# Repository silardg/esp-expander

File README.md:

# esp-expander

## Main Components
- ESP32-WROOM-32D
- LAN8720
- MCP23017

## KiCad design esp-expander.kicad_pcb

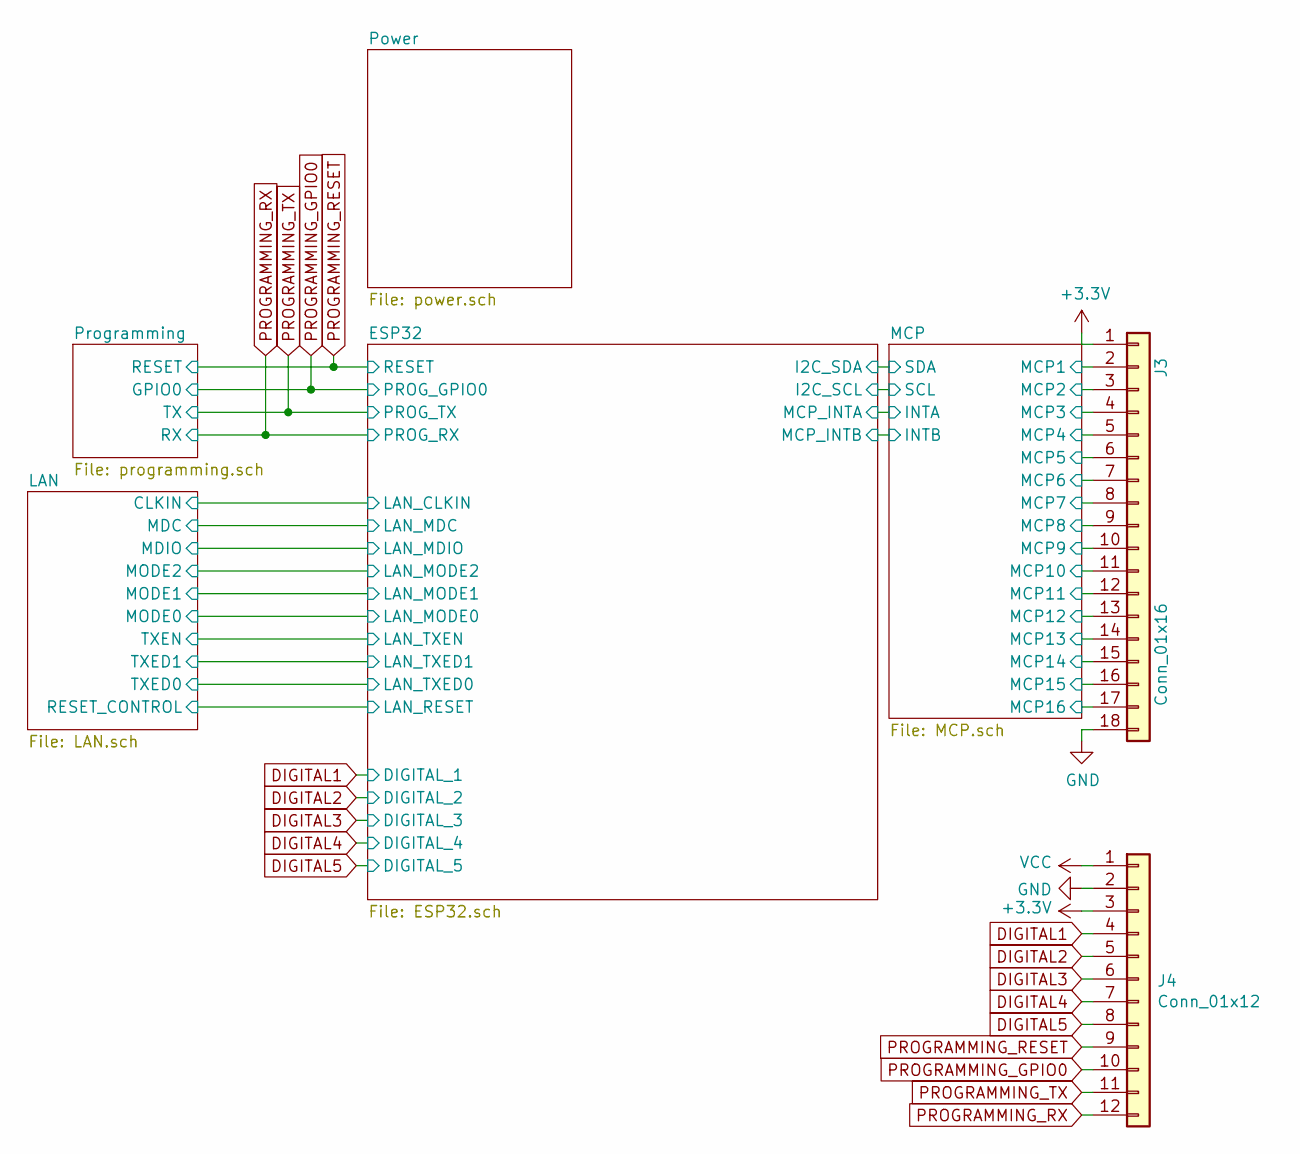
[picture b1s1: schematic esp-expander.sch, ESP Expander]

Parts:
J3: Conn_01x16; PinHeader_1x18_P2.54mm_Vertical; LCSC C725948
J4: Conn_01x12; PinHeader_1x12_P2.54mm_Vertical; LCSC C225487

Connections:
+3V3: J3.1, J4.3; also elsewhere on the board
/MCP/MCP1: J3.2; also elsewhere on the board
/MCP/MCP2: J3.3; also elsewhere on the board
/MCP/MCP3: J3.4; also elsewhere on the board
/MCP/MCP4: J3.5; also elsewhere on the board
/MCP/MCP5: J3.6; also elsewhere on the board
/MCP/MCP6: J3.7; also elsewhere on the board
/MCP/MCP7: J3.8; also elsewhere on the board
/MCP/MCP8: J3.9; also elsewhere on the board
/MCP/MCP9: J3.10; also elsewhere on the board
/MCP/MCP10: J3.11; also elsewhere on the board
/MCP/MCP11: J3.12; also elsewhere on the board
/MCP/MCP12: J3.13; also elsewhere on the board
/MCP/MCP13: J3.14; also elsewhere on the board
/MCP/MCP14: J3.15; also elsewhere on the board
/MCP/MCP15: J3.16; also elsewhere on the board
/MCP/MCP16: J3.17; also elsewhere on the board
DIGITAL1: J4.4; also elsewhere on the board
DIGITAL2: J4.5; also elsewhere on the board
DIGITAL3: J4.6; also elsewhere on the board
DIGITAL4: J4.7; also elsewhere on the board
DIGITAL5: J4.8; also elsewhere on the board
GND: J3.18, J4.2; also elsewhere on the board
PROGRAMMING_GPIO0: J4.10; also elsewhere on the board
PROGRAMMING_RESET: J4.9; also elsewhere on the board
PROGRAMMING_RX: J4.12; also elsewhere on the board
PROGRAMMING_TX: J4.11; also elsewhere on the board
VCC: J4.1; also elsewhere on the board

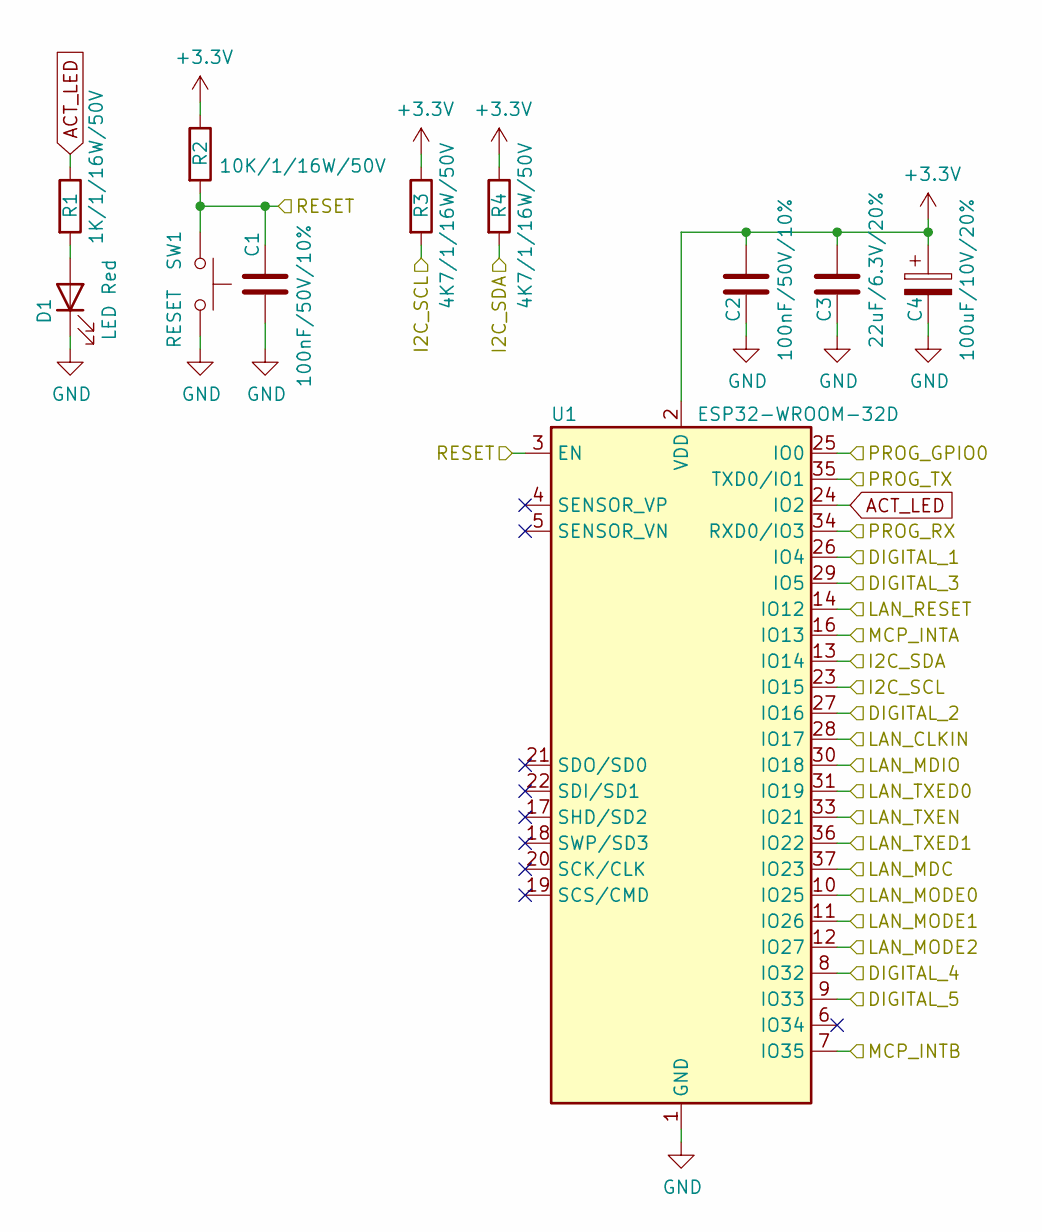
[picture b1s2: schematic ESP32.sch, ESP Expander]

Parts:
C1, C2: 100nF/50V/10%; C_0402_1005Metric; LCSC C307331
C3: 22uF/6.3V/20%; C_0402_1005Metric; LCSC C415703
C4: 100uF/10V/20%; CP_Elec_5x5.4; LCSC C96182
D1: LED Red; LED_0603_1608Metric; LCSC C2286
R1: 1K/1/16W/50V; R_0402_1005Metric; LCSC C11702
R2: 10K/1/16W/50V; R_0402_1005Metric; LCSC C25744
R3, R4: 4K7/1/16W/50V; R_0402_1005Metric; LCSC C25900
SW1: RESET; SW_SPST_EVPBF; LCSC C318884
U1: ESP32-WROOM-32D; ESP32-WROOM-32; LCSC C473012

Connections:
+3V3: C2.1, C3.1, C4.1, R2.1, R3.1, R4.1, U1.2 (VDD); also elsewhere on the board
/ESP32/I2C_SCL: R3.2, U1.23 (IO15); also elsewhere on the board
/ESP32/I2C_SDA: R4.2, U1.13 (IO14); also elsewhere on the board
/ESP32/LAN_MDC: U1.37 (IO23); also elsewhere on the board
/ESP32/LAN_MDIO: U1.30 (IO18); also elsewhere on the board
/ESP32/LAN_MODE0: U1.10 (IO25); also elsewhere on the board
/ESP32/LAN_MODE1: U1.11 (IO26); also elsewhere on the board
/ESP32/LAN_MODE2: U1.12 (IO27); also elsewhere on the board
/ESP32/LAN_RESET: U1.14 (IO12); also elsewhere on the board
/ESP32/LAN_TXED0: U1.31 (IO19); also elsewhere on the board
/ESP32/LAN_TXED1: U1.36 (IO22); also elsewhere on the board
/ESP32/LAN_TXEN: U1.33 (IO21); also elsewhere on the board
/LAN/CLKIN: U1.28 (IO17); also elsewhere on the board
/MCP/INTA: U1.16 (IO13); also elsewhere on the board
/MCP/INTB: U1.7 (IO35); also elsewhere on the board
ACT_LED: R1.1, U1.24 (IO2)
DIGITAL1: U1.26 (IO4); also elsewhere on the board
DIGITAL2: U1.27 (IO16); also elsewhere on the board
DIGITAL3: U1.29 (IO5); also elsewhere on the board
DIGITAL4: U1.8 (IO32); also elsewhere on the board
DIGITAL5: U1.9 (IO33); also elsewhere on the board
GND: C1.2, C2.2, C3.2, C4.2, D1.1 (K), SW1.1, U1.1 (GND), U1.15 (GND), U1.38 (GND), U1.39 (GND); also elsewhere on the board
unnamed: D1.2 (A), R1.2
PROGRAMMING_GPIO0: U1.25 (IO0); also elsewhere on the board
PROGRAMMING_RESET: C1.1, R2.2, SW1.2, U1.3 (EN); also elsewhere on the board
PROGRAMMING_RX: U1.34 (RXD0/IO3); also elsewhere on the board
PROGRAMMING_TX: U1.35 (TXD0/IO1); also elsewhere on the board

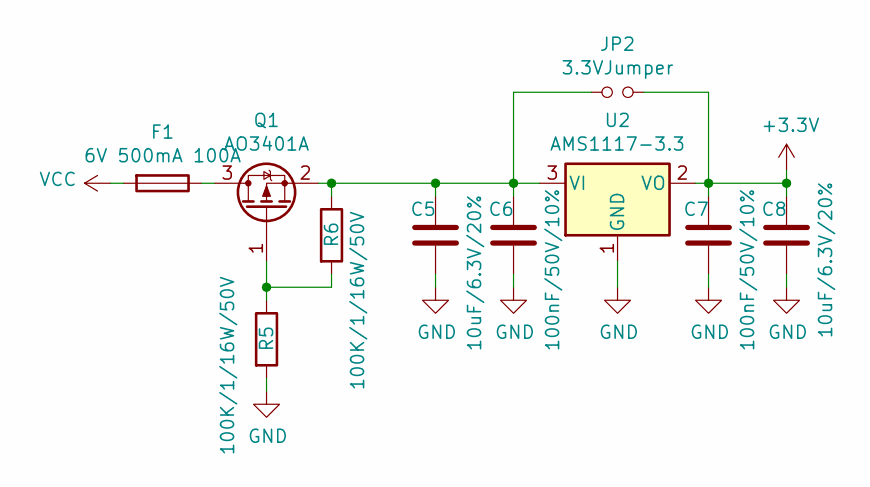
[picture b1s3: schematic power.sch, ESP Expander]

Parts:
C5, C8: 10uF/6.3V/20%; C_0402_1005Metric; LCSC C15525
C6, C7: 100nF/50V/10%; C_0402_1005Metric; LCSC C307331
F1: 6V 500mA 100A; Fuse_0805_2012Metric; LCSC C135329
JP2: 3.3VJumper; SolderJumper-2_P1.3mm_Open_Pad1.0x1.5mm
Q1: AO3401A; SOT-23; LCSC C15127
R5, R6: 100K/1/16W/50V; R_0402_1005Metric; LCSC C25741
U2: AMS1117-3.3; SOT-223-3_TabPin2; LCSC C6186

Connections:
+3V3: C7.1, C8.1, JP2.2, U2.2 (VO); also elsewhere on the board
GND: C5.2, C6.2, C7.2, C8.2, R5.2, U2.1 (GND); also elsewhere on the board
unnamed: C5.1, C6.1, JP2.1, Q1.2 (S), R6.1, U2.3 (VI)
unnamed: F1.1, Q1.3 (D)
unnamed: Q1.1 (G), R5.1, R6.2
VCC: F1.2; also elsewhere on the board

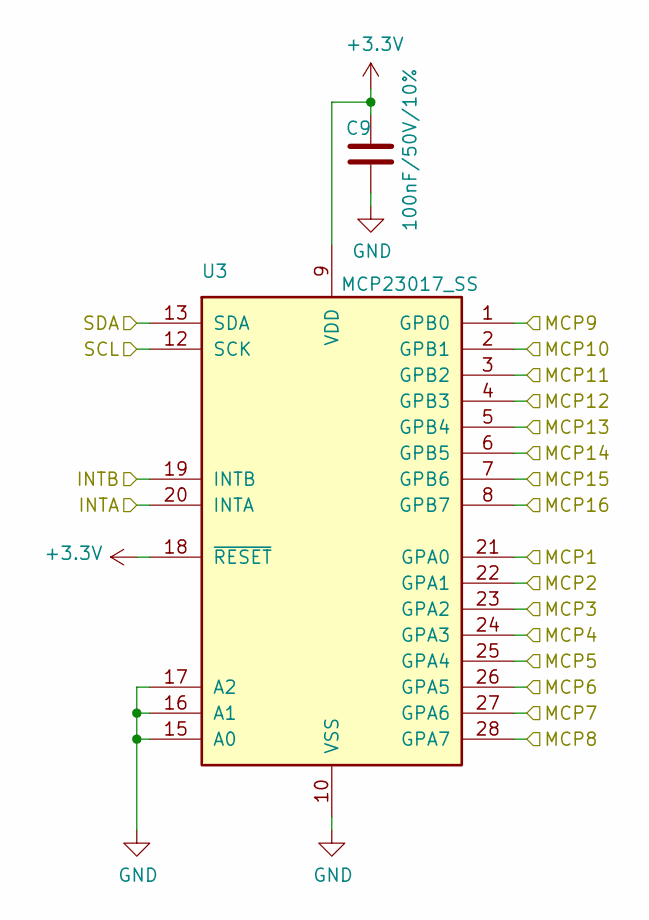
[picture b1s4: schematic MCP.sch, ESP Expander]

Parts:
C9: 100nF/50V/10%; C_0402_1005Metric; LCSC C307331
U3: MCP23017_SS; SSOP-28_5.3x10.2mm_P0.65mm; LCSC C153287

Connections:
+3V3: C9.1, U3.9 (VDD), U3.18 (~RESET~); also elsewhere on the board
/ESP32/I2C_SCL: U3.12 (SCK); also elsewhere on the board
/ESP32/I2C_SDA: U3.13 (SDA); also elsewhere on the board
/MCP/INTA: U3.20 (INTA); also elsewhere on the board
/MCP/INTB: U3.19 (INTB); also elsewhere on the board
/MCP/MCP1: U3.21 (GPA0); also elsewhere on the board
/MCP/MCP2: U3.22 (GPA1); also elsewhere on the board
/MCP/MCP3: U3.23 (GPA2); also elsewhere on the board
/MCP/MCP4: U3.24 (GPA3); also elsewhere on the board
/MCP/MCP5: U3.25 (GPA4); also elsewhere on the board
/MCP/MCP6: U3.26 (GPA5); also elsewhere on the board
/MCP/MCP7: U3.27 (GPA6); also elsewhere on the board
/MCP/MCP8: U3.28 (GPA7); also elsewhere on the board
/MCP/MCP9: U3.1 (GPB0); also elsewhere on the board
/MCP/MCP10: U3.2 (GPB1); also elsewhere on the board
/MCP/MCP11: U3.3 (GPB2); also elsewhere on the board
/MCP/MCP12: U3.4 (GPB3); also elsewhere on the board
/MCP/MCP13: U3.5 (GPB4); also elsewhere on the board
/MCP/MCP14: U3.6 (GPB5); also elsewhere on the board
/MCP/MCP15: U3.7 (GPB6); also elsewhere on the board
/MCP/MCP16: U3.8 (GPB7); also elsewhere on the board
GND: C9.2, U3.10 (VSS), U3.15 (A0), U3.16 (A1), U3.17 (A2); also elsewhere on the board

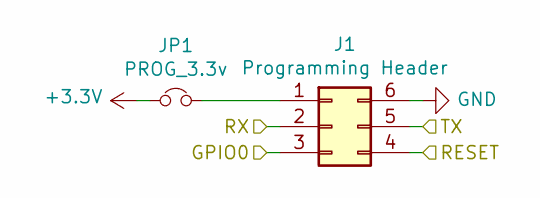
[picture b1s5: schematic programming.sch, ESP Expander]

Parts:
J1: Programming Header; Tag-Connect_TC2030-IDC-NL_2x03_P1.27mm_Vertical
JP1: PROG_3.3v; SolderJumper-2_P1.3mm_Bridged_Pad1.0x1.5mm

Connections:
+3V3: JP1.1; also elsewhere on the board
GND: J1.6; also elsewhere on the board
unnamed: J1.1, JP1.2
PROGRAMMING_GPIO0: J1.3; also elsewhere on the board
PROGRAMMING_RESET: J1.4; also elsewhere on the board
PROGRAMMING_RX: J1.2; also elsewhere on the board
PROGRAMMING_TX: J1.5; also elsewhere on the board

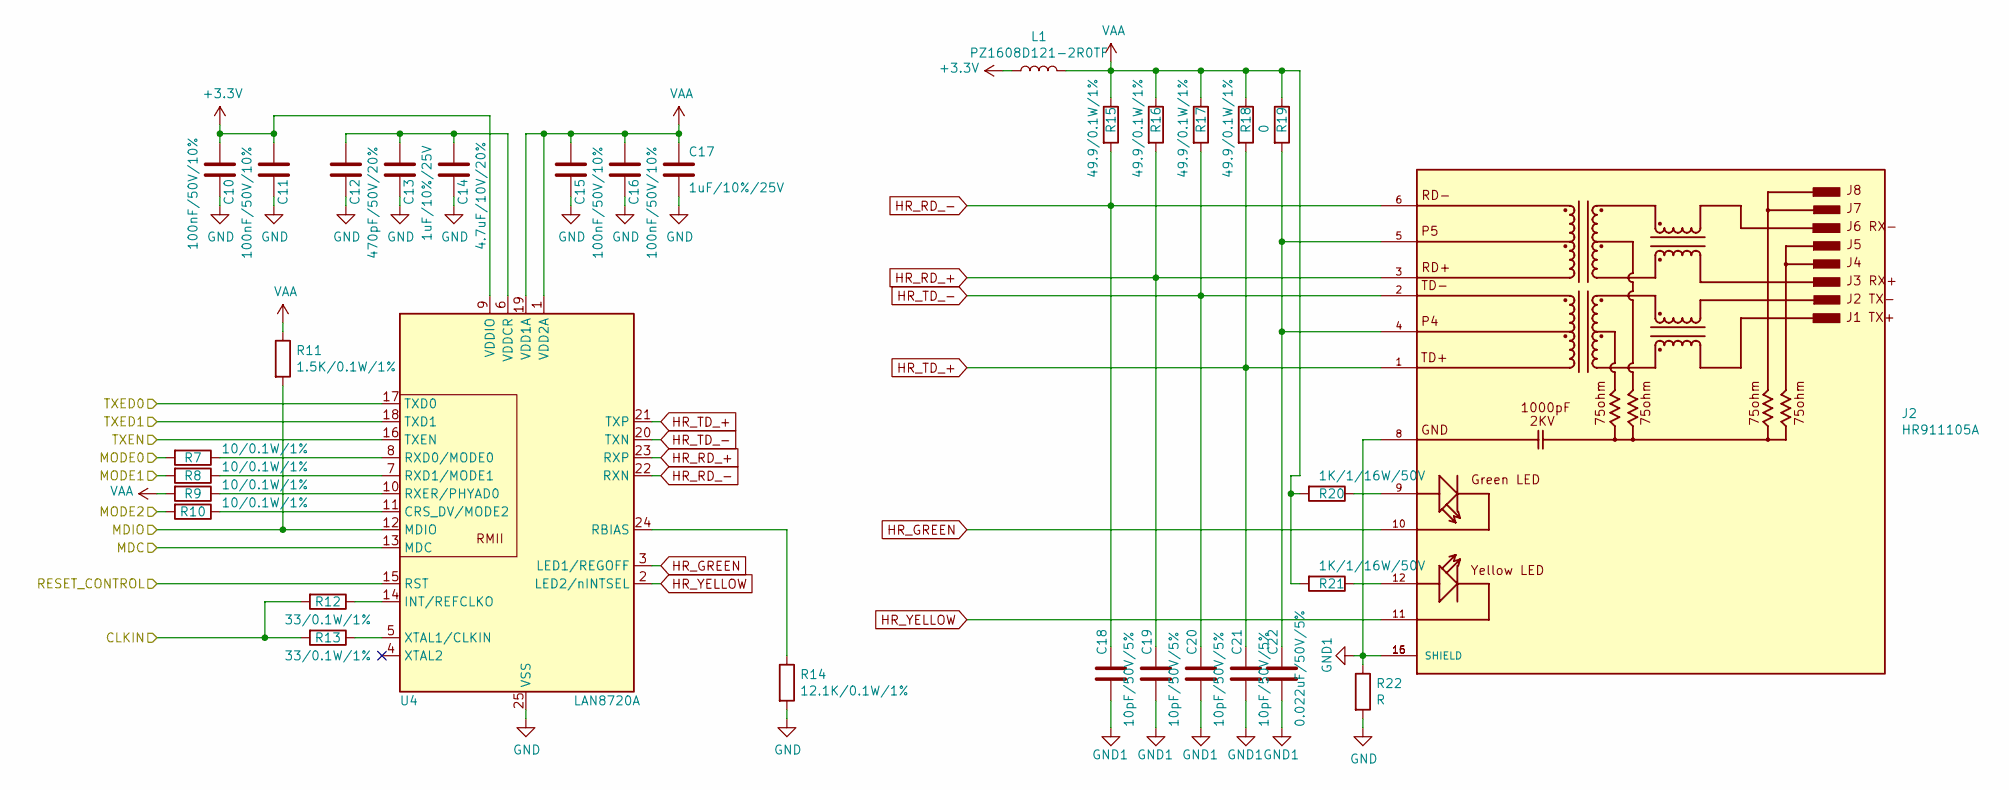
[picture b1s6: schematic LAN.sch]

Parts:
C10, C11, C15, C16: 100nF/50V/10%; C_0402_1005Metric; LCSC C307331
C12: 470pF/50V/20%; C_0402_1005Metric; LCSC C1537
C13, C17: 1uF/10%/25V; C_0402_1005Metric; LCSC C52923
C14: 4.7uF/10V/20%; C_0402_1005Metric; LCSC C23733
C18, C19, C20, C21: 10pF/50V/5%; C_0402_1005Metric; LCSC C32949
C22: 0.022uF/50V/5%; C_0402_1005Metric; LCSC C1531
J2: HR911105A; HANRUN_HR911105A; PARTREV A; LCSC C12074
L1: PZ1608D121-2R0TF; L_0603_1608Metric; LCSC C42102
R7, R8, R9, R10: 10/0.1W/1%; R_0402_1005Metric; LCSC C25077
R11: 1.5K/0.1W/1%; R_0402_1005Metric; LCSC C25867
R12, R13: 33/0.1W/1%; R_0402_1005Metric; LCSC C25105
R14: 12.1K/0.1W/1%; R_0402_1005Metric; LCSC C321280
R15, R16, R17, R18: 49.9/0.1W/1%; R_0402_1005Metric; LCSC C25120
R19: 0; R_0402_1005Metric; LCSC C17168
R20, R21: 1K/1/16W/50V; R_0402_1005Metric; LCSC C11702
R22: R; R_1206_3216Metric; LCSC C17888
U4: LAN8720A; QFN-24-1EP_4x4mm_P0.5mm_EP2.6x2.6mm; LCSC C45223

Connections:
+3V3: C10.1, C11.1, L1.1, U4.9 (VDDIO); also elsewhere on the board
/ESP32/LAN_MDC: U4.13 (MDC); also elsewhere on the board
/ESP32/LAN_MDIO: R11.2, U4.12 (MDIO); also elsewhere on the board
/ESP32/LAN_MODE0: R7.2; also elsewhere on the board
/ESP32/LAN_MODE1: R8.2; also elsewhere on the board
/ESP32/LAN_MODE2: R10.2; also elsewhere on the board
/ESP32/LAN_RESET: U4.15 (RST); also elsewhere on the board
/ESP32/LAN_TXED0: U4.17 (TXD0); also elsewhere on the board
/ESP32/LAN_TXED1: U4.18 (TXD1); also elsewhere on the board
/ESP32/LAN_TXEN: U4.16 (TXEN); also elsewhere on the board
/LAN/CLKIN: R12.2, R13.2; also elsewhere on the board
GND: C10.2, C11.2, C12.2, C13.2, C14.2, C15.2, C16.2, C17.2, R14.2, R22.2, U4.25 (VSS); also elsewhere on the board
GND1: C18.2, C19.2, C20.2, C21.2, C22.2, J2.8, J2.15 (SHIELD), J2.16 (SHIELD), R22.1
HR_GREEN: J2.10, U4.3 (LED1/REGOFF)
HR_RD_+: C19.1, J2.3, R16.2, U4.23 (RXP)
HR_RD_-: C18.1, J2.6, R15.2, U4.22 (RXN)
HR_TD_+: C21.1, J2.1, R18.2, U4.21 (TXP)
HR_TD_-: C20.1, J2.2, R17.2, U4.20 (TXN)
HR_YELLOW: J2.11, U4.2 (LED2/nINTSEL)
unnamed: C12.1, C13.1, C14.1, U4.6 (VDDCR)
unnamed: C22.1, J2.4, J2.5, R19.2
unnamed: J2.9, R20.1
unnamed: J2.12, R21.1
unnamed: R7.1, U4.8 (RXD0/MODE0)
unnamed: R8.1, U4.7 (RXD1/MODE1)
unnamed: R9.1, U4.10 (RXER/PHYAD0)
unnamed: R10.1, U4.11 (CRS_DV/MODE2)
unnamed: R12.1, U4.14 (INT/REFCLKO)
unnamed: R13.1, U4.5 (XTAL1/CLKIN)
unnamed: R14.1, U4.24 (RBIAS)
VAA: C15.1, C16.1, C17.1, L1.2, R9.2, R11.1, R15.1, R16.1, R17.1, R18.1, R19.1, R20.2, R21.2, U4.1 (VDD2A), U4.19 (VDD1A)

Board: 2 copper layers, 59 parts (2 on the bottom side), 67 nets, no tracks yet.

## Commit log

2022-02-20 Added project
2022-02-20 A bit of readme
2022-02-20 Added esp32 part
2022-02-20 Added power and mcp
2022-02-20 Added labels
2022-02-20 Added programming port
2022-02-21 Added LAN circuit
2022-02-21 Exported first net
2022-02-21 Added to pcb
2022-02-21 Added lcsc part nums
2022-02-21 Removed all the silk
2022-02-22 Added schematic
2022-02-22 Added bom
2022-02-23 Basic layout done
2022-02-26 Added unfinished pics
2022-02-26 Added test manufacturing files
